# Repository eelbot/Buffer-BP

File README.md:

# Buffer Booster Pack
## Overview
The Buffer Booster Pack is a simple Booster Pack for TI's LaunchPad development ecosystem that connects eight 5V inputs and eight 5V outputs to the 3.3V inputs and outputs of the LaunchPad. There are indicators and screw terminal connections for each input, as well as screw terminals connections for 5V and GND, to easily interface with proto-typed circuits.

## Pinout
The Buffer Booster Pack is made for a 40-pin booster pack, and follows the Booster Pack Standard. The external input and output numbering is shown on the board.

| External Input | Booster Pack Pin # | | External Output | Booster Pack Pin # |
| :------------: | :------------------: | :--: | :-------------: | :------------------: |
| 1 | 7 | | 1 | 38 |
| 2 | 8 | | 2 | 37 |
| 3 | 9 | | 3 | 15 |
| 4 | 10 | | 4 | 14 |
| 5 | 5 | | 5 | 34 |
| 6 | 39 | | 6 | 13 |
| 7 | 40 | | 7 | 12 |
| 8 | 19 | | 8 | 11 |

## Firmware Examples
Two examples are included in the firmware folder. There is one for Energia, which uses standard Booster Pack pinouts, and the other is for the F28069 LaunchPad with Code Composer Studio.

## Power
The Buffer Booster Pack supplies 3.3V to the 3V3 pin of the target Launchpad. The 5V pin is not connected, and the external DC Jack must be connected in order for the Booster Pack to function correctly.

## To-Do
- Final hardware tests (need to wait until boards arrive)

## License
<br>
This work is licensed under a [Creative Commons Attribution-ShareAlike 3.0 Unported License](http://creativecommons.org/licenses/by-sa/3.0/)

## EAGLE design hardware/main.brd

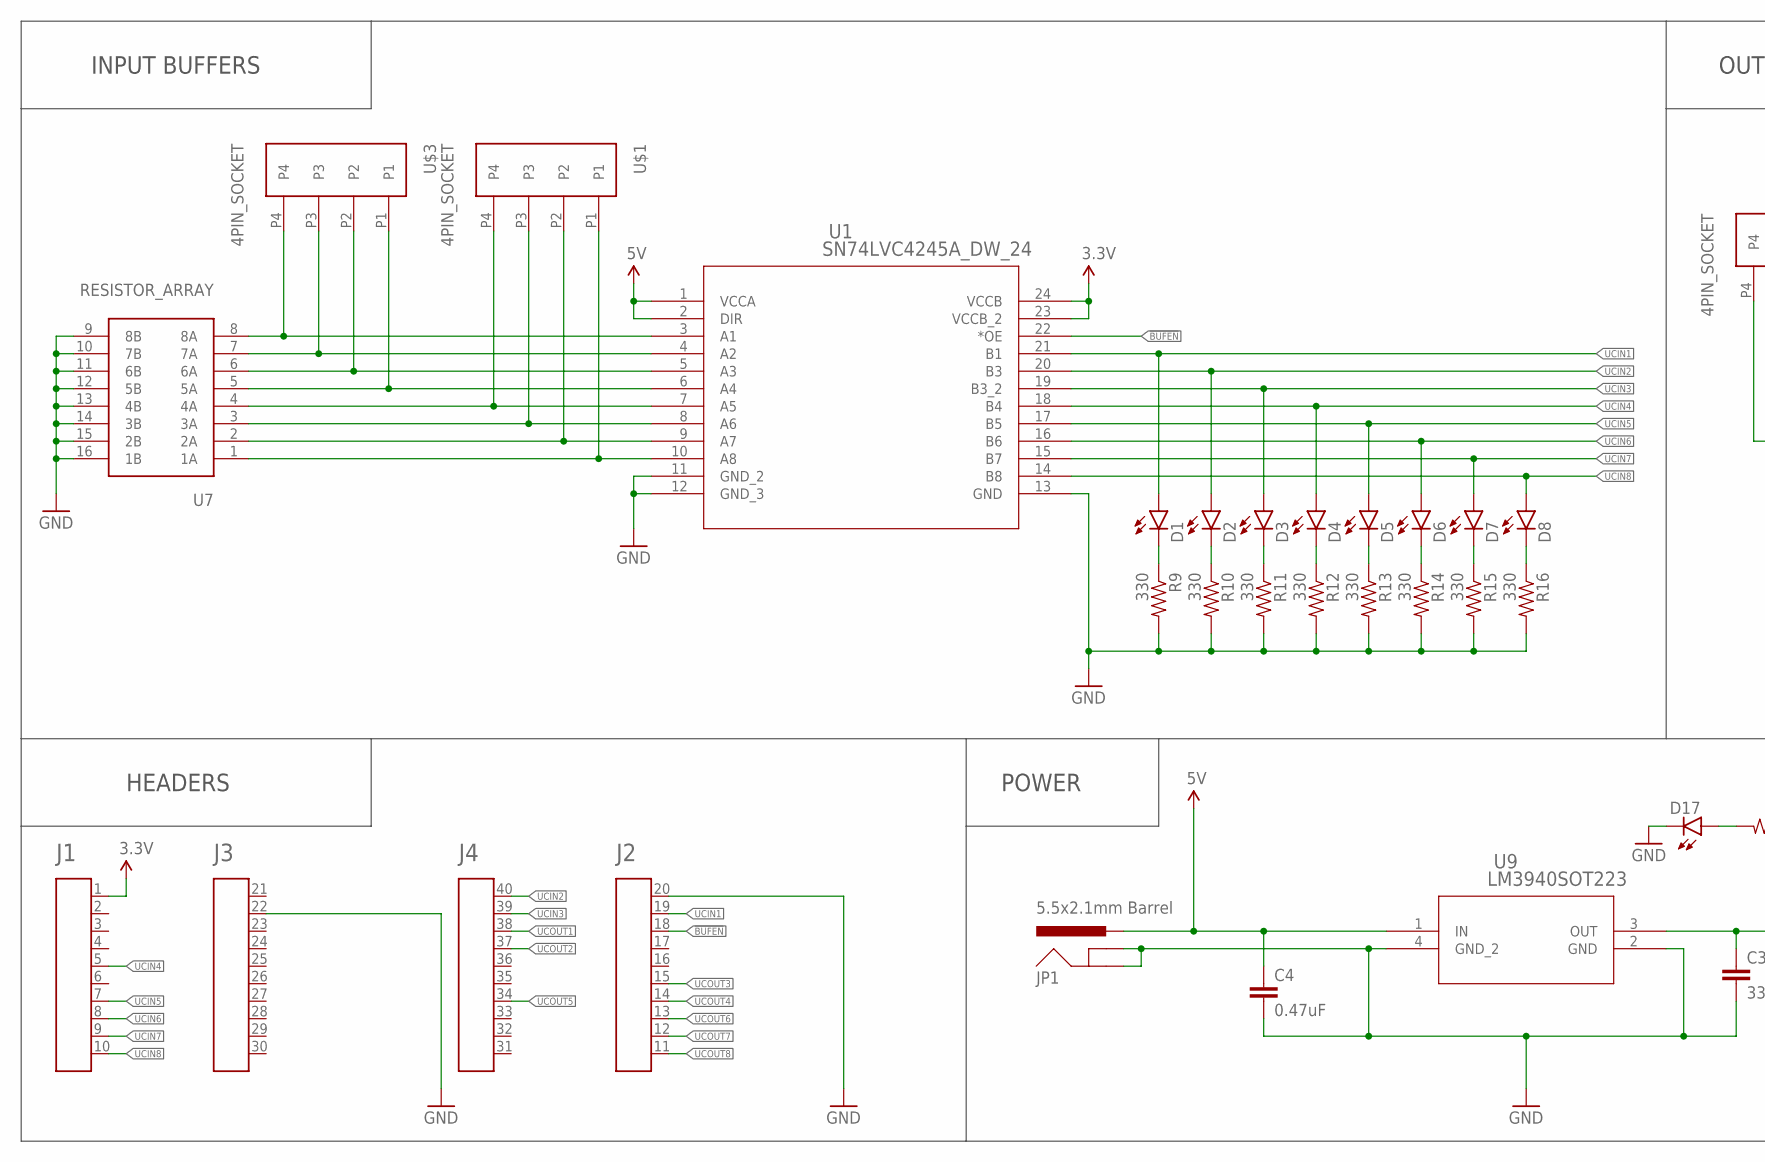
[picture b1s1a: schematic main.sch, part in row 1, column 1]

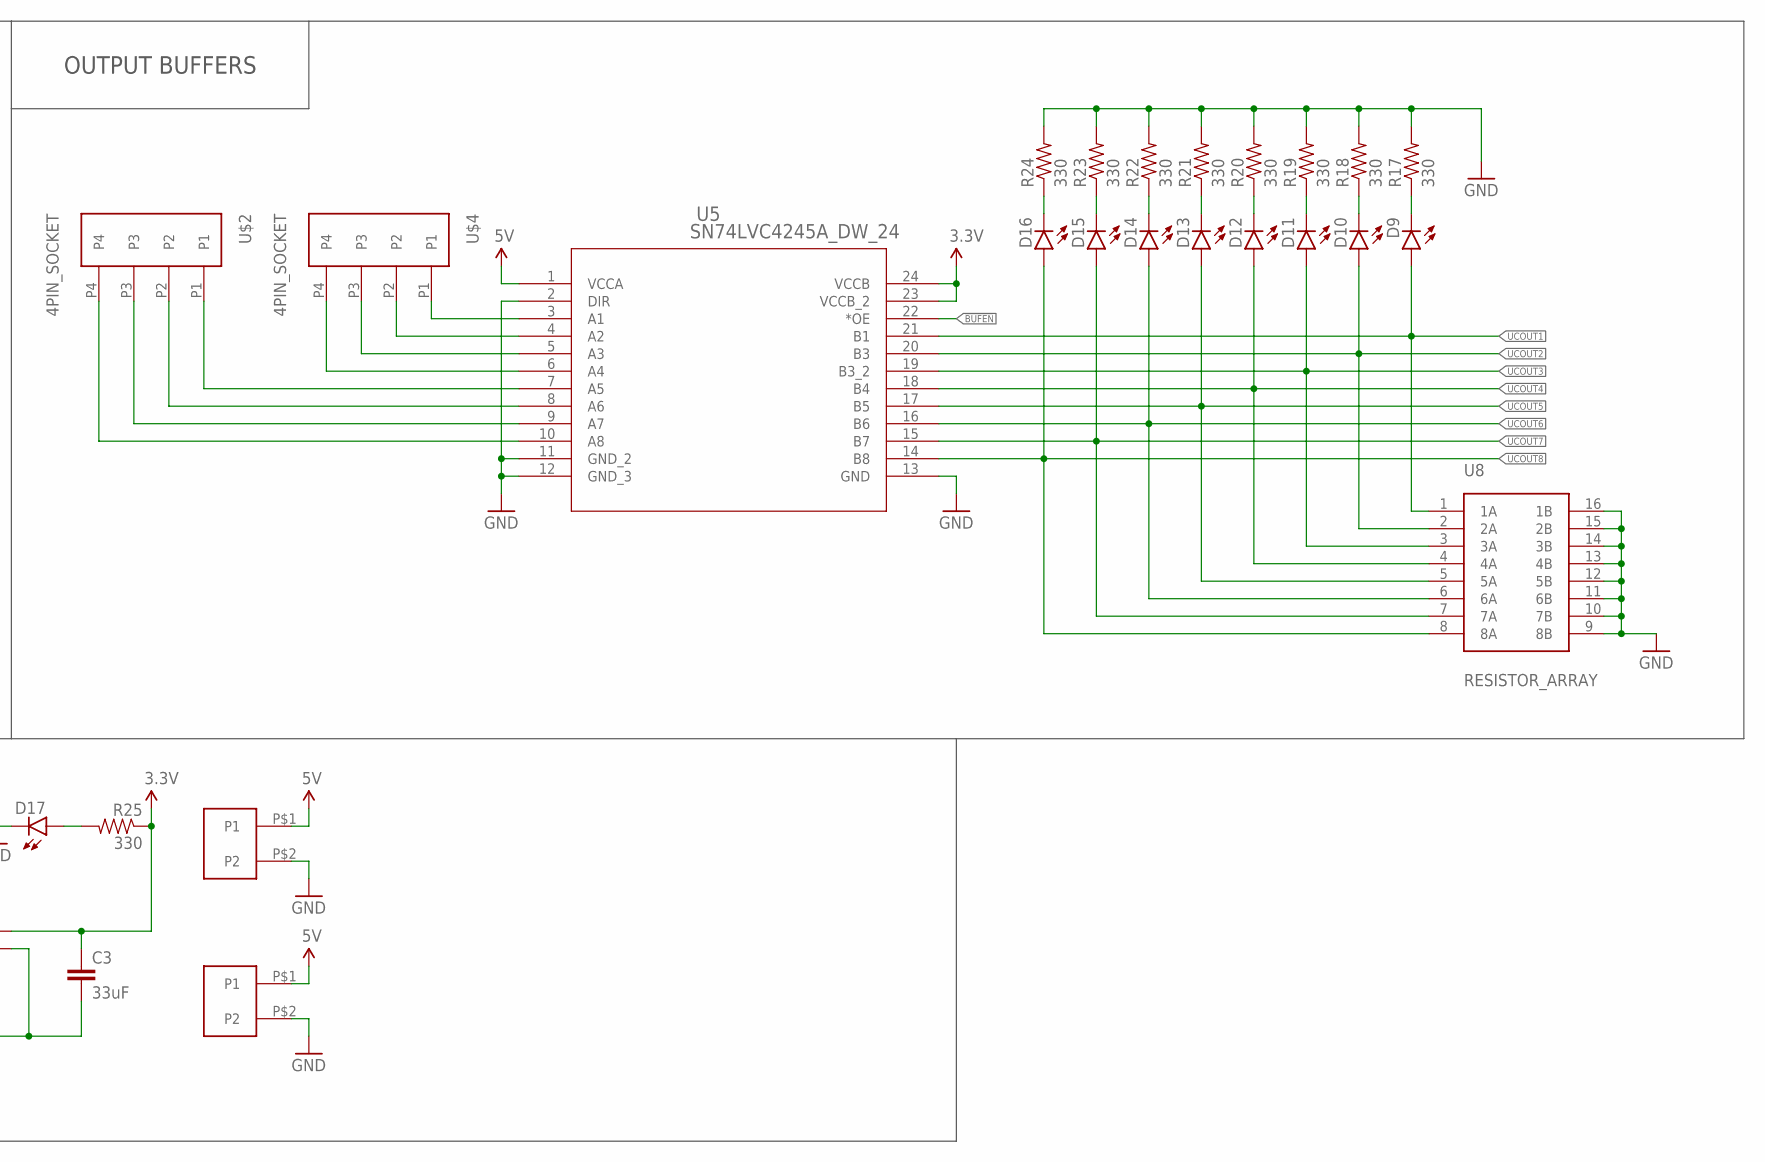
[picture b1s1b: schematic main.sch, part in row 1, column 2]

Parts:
A1: HEADER4X10-BOOSTERPACK; 4X10-BOOSTERPACK
C3: 33uF; 1206
C4: 0.47uF; 0805
D1, D2, D3, D4, D5, D6, D7, D8, D9, D10, D11, D12, D13, D14, D15, D16, D17: LED3MM
JP1: 5.5x2.1mm Barrel; POWER_JACK_SMD
R9, R10, R11, R12, R13, R14, R15, R16, R17, R18, R19, R20, R21, R22, R23, R24, R25: 330; 0805
U1, U5: SN74LVC4245A_DW_24; DW24
U7, U8: RESISTOR_ARRAY; DIL16
U9: LM3940SOT223; DCY
U$1, U$2, U$3, U$4: 4PIN_SOCKET; CONN-4PIN
U$5, U$6: 2PIN_SOCKET; CONN-2PIN

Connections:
3.3V: A1.1, C3.1, R25.1, U1.23 (VCCB_2), U1.24 (VCCB), U5.23 (VCCB_2), U5.24 (VCCB), U9.3 (OUT)
5V: C4.1, JP1.VIN0 (PWR), U1.1 (VCCA), U1.2 (DIR), U5.1 (VCCA), U9.1 (IN), U$5.P$1 (P1), U$6.P$1 (P1)
!BUFEN!: A1.18, U1.22 (*OE), U5.22 (*OE)
GND: A1.20, A1.22, C3.2, C4.2, D17.K (C), JP1.GND (GNDBREAK), JP1.P$4 (GND), R9.2, R10.2, R11.2, R12.2, R13.2, R14.2, R15.2, R16.2, R17.2, R18.2, R19.2, R20.2, R21.2, R22.2, R23.2, R24.2, U1.11 (GND_2), U1.12 (GND_3), U1.13 (GND), U5.2 (DIR), U5.11 (GND_2), U5.12 (GND_3), U5.13 (GND), U7.9 (8B), U7.10 (7B), U7.11 (6B), U7.12 (5B), U7.13 (4B), U7.14 (3B), U7.15 (2B), U7.16 (1B), U8.9 (8B), U8.10 (7B), U8.11 (6B), U8.12 (5B), U8.13 (4B), U8.14 (3B), U8.15 (2B), U8.16 (1B), U9.2 (GND), U9.4 (GND_2), U$5.P$2 (P2), U$6.P$2 (P2)
unnamed: U1.10 (A8), U7.1 (1A), U$1.P1
unnamed: U1.9 (A7), U7.2 (2A), U$1.P2
unnamed: U1.8 (A6), U7.3 (3A), U$1.P3
unnamed: U1.7 (A5), U7.4 (4A), U$1.P4
unnamed: U1.6 (A4), U7.5 (5A), U$3.P1
unnamed: U1.5 (A3), U7.6 (6A), U$3.P2
unnamed: U1.4 (A2), U7.7 (7A), U$3.P3
unnamed: U1.3 (A1), U7.8 (8A), U$3.P4
unnamed: D1.K (C), R9.1
unnamed: D2.K (C), R10.1
unnamed: D3.K (C), R11.1
unnamed: D4.K (C), R12.1
unnamed: D5.K (C), R13.1
unnamed: D6.K (C), R14.1
unnamed: D7.K (C), R15.1
unnamed: D8.K (C), R16.1
unnamed: U5.3 (A1), U$4.P1
unnamed: U5.4 (A2), U$4.P2
unnamed: U5.5 (A3), U$4.P3
unnamed: U5.6 (A4), U$4.P4
unnamed: U5.7 (A5), U$2.P1
unnamed: U5.8 (A6), U$2.P2
unnamed: U5.9 (A7), U$2.P3
unnamed: U5.10 (A8), U$2.P4
unnamed: D9.K (C), R17.1
unnamed: D10.K (C), R18.1
unnamed: D11.K (C), R19.1
unnamed: D12.K (C), R20.1
unnamed: D13.K (C), R21.1
unnamed: D14.K (C), R22.1
unnamed: D15.K (C), R23.1
unnamed: D16.K (C), R24.1
unnamed: D17.A, R25.2
UCIN1: A1.19, D1.A, U1.21 (B1)
UCIN2: A1.40, D2.A, U1.20 (B3)
UCIN3: A1.39, D3.A, U1.19 (B3_2)
UCIN4: A1.5, D4.A, U1.18 (B4)
UCIN5: A1.7, D5.A, U1.17 (B5)
UCIN6: A1.8, D6.A, U1.16 (B6)
UCIN7: A1.9, D7.A, U1.15 (B7)
UCIN8: A1.10, D8.A, U1.14 (B8)
UCOUT1: A1.38, D9.A, U5.21 (B1), U8.1 (1A)
UCOUT2: A1.37, D10.A, U5.20 (B3), U8.2 (2A)
UCOUT3: A1.15, D11.A, U5.19 (B3_2), U8.3 (3A)
UCOUT4: A1.14, D12.A, U5.18 (B4), U8.4 (4A)
UCOUT5: A1.34, D13.A, U5.17 (B5), U8.5 (5A)
UCOUT6: A1.13, D14.A, U5.16 (B6), U8.6 (6A)
UCOUT7: A1.12, D15.A, U5.15 (B7), U8.7 (7A)
UCOUT8: A1.11, D16.A, U5.14 (B8), U8.8 (8A)

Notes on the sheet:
INPUT BUFFERS
HEADERS
OUTPUT BUFFERS
POWER

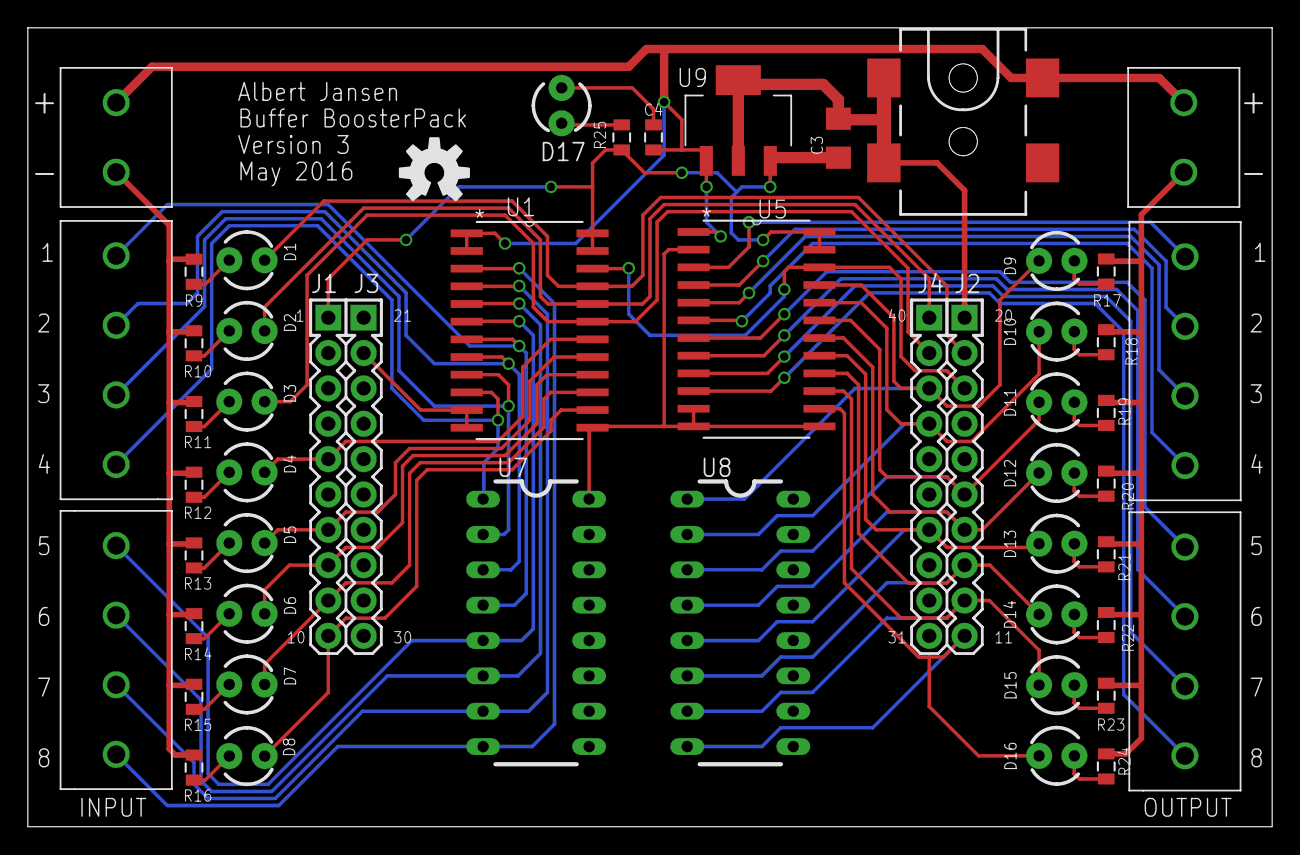
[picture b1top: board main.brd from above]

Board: 2 copper layers, 89.4 x 57.4 mm, 50 parts (0 on the bottom side), 53 nets.

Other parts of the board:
U$7: OSHW-LOGO-M

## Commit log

2016-04-03 Designed schematic and routed board.
2016-04-03 Cleaned up board. Cleaned up schematic. No structural or electrical changes
2016-04-04 Minor fixes and gerber generation
2016-04-04 Gerbers generated - Elecrow 2 layers
2016-04-15 Added pulldown resistors on inputs. Updated version number
2016-05-11 Re-routed and updated board and schematic
2016-05-11 Cleaned up and finalized board design
2016-05-11 Updated with DRC modifications
2016-05-18 Minor component value changes. Added a BOM
2016-05-18 Added an Energia example
2016-05-18 Removed 'ENEXT', as it is not needed
2016-05-18 Added code for F28069 Launchpad, renamed Energia folder
2016-05-18 Added helpful silkscreen markings
2016-05-20 Small power routing update (Power the target launchpad via 3.3V connection)
2016-05-20 Finalized documentation and added open source licensing and logos
2016-05-20 Updated table
2016-05-26 Added proper .gitignore

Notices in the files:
parts and their libraries:
SparkFun-Resistors: Licensing: Creative Commons ShareAlike 4.0 International - https://creativecommons.org/licenses/by-sa/4.0
